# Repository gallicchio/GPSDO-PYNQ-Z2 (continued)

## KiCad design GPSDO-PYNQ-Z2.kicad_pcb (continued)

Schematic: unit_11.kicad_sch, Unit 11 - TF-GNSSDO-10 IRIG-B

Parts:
C1101: 10n C0G; C_0805_2012Metric
C1102, C1104, C1106, C1108: 100n; C_0805_2012Metric
C1103, C1105, C1107, C1109: 10n; C_0805_2012Metric
D1101: BAV99; SOT-23; LCSC C916421; not fitted
J1101: 10MHz IN; SMA_Vertical_THT_Universal; LCSC C496549
J1102: 1pps IN; SMA_Vertical_THT_Universal; LCSC C496549
J1103: TAP IN; U.FL_Hirose_U.FL-R-SMT-1_Vertical; LCSC C88374
J1104: TAP SQ; U.FL_Hirose_U.FL-R-SMT-1_Vertical; LCSC C88374
JP1101: 50R/PARK; PinHeader_1x03_P2.54mm_Vertical
R1101: 51R 1%; R_0805_2012Metric
R1102: 0R; R_0805_2012Metric
R1103: 2k2; R_0805_2012Metric
R1104: 330R; R_0805_2012Metric
R1105: 1M 1%; R_0805_2012Metric
R1106: 51R; R_0805_2012Metric; not fitted
R1107, R1121, R1123: 1k; R_0805_2012Metric
R1108: 10k; R_0805_2012Metric
R1122: 100k; R_0805_2012Metric
R1151, R1152, R1153, R1154: 4R7; R_0805_2012Metric
TP1101: TP_IN; TestPoint_Pad_D1.5mm
TP1102: TP_SQ; TestPoint_Pad_D1.5mm
TP1103: TP_BEAT; TestPoint_Pad_D1.5mm
TP1104: TP_PPS; TestPoint_Pad_D1.5mm
U1101: 74LVC2GU04; SOT-363_SC-70-6; LCSC C116660
U1102, U1103: 74LVC1G80; SOT-23-5; LCSC C42879
U1104: 74LVC1G17; SOT-23-5; LCSC C7836

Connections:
+3V3_A: D1101.1 (K), R1151.1, R1152.1, R1153.1, R1154.1; also elsewhere on the board
/Unit 11/PARK: JP1101.3, R1122.2
/Unit 11/REPLICA: R1105.2, U1101.3 (2A), U1101.4 (2Y)
BEAT_10: TP1103.1, U1103.4 (~Q); also elsewhere on the board
GND: C1102.2, C1103.2, C1104.2, C1105.2, C1106.2, C1107.2, C1108.2, C1109.2, D1101.2 (A), J1101.2 (Ext), J1102.2 (Ext), J1103.2 (Ext), J1104.2 (Ext), JP1101.2, R1103.2, R1106.2, R1108.2, U1101.2 (GND), U1102.3 (GND), U1103.3 (GND), U1104.3 (GND); also elsewhere on the board
HCLK_10: U1102.2 (C), U1103.2 (C); also elsewhere on the board
unnamed: C1101.1, R1102.2, R1103.1, R1121.2
unnamed: C1101.2, D1101.3 (K), R1104.1
unnamed: J1101.1 (In), R1101.1, R1102.1, TP1101.1
unnamed: J1102.1 (In), R1106.1, R1107.1
unnamed: J1103.1 (In), R1121.1
unnamed: J1104.1 (In), R1123.1
unnamed: JP1101.1, R1101.2
unnamed: R1107.2, R1108.1, U1104.2
unnamed: R1104.2, R1105.1, R1122.1, TP1102.1, U1101.1 (1A)
unnamed: R1123.2, U1101.6 (1Y), U1102.1 (D)
unnamed: C1102.1, C1103.1, R1151.2, U1101.5 (VCC)
unnamed: C1104.1, C1105.1, R1152.2, U1102.5 (VCC)
unnamed: U1102.4 (~Q), U1103.1 (D)
unnamed: C1106.1, C1107.1, R1153.2, U1103.5 (VCC)
unnamed: C1108.1, C1109.1, R1154.2, U1104.5 (VCC)
PPS_10: TP1104.1, U1104.4; also elsewhere on the board

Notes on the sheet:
2-3 = PARK: source off or unplugged (not 50R)
into FF1.D: 0/3.3 V CMOS at 10 MHz, edges ~1-2 ns
is plugged in
AC couple
DNP: nothing here drives 50 ohm
REPLICA BIAS. Half 2, its input tied to its output, sits at
10 MHz DDMTD front end + 1 pps front end. Every unit sheet has this same layout; only the names, the per-channel population and the expected levels differ.
DNP clamp: fit only for an unterminated hot source
OUT BEAT_10 -> sheet 'RPi header' OUT PPS_10 -> sheet 'RPi header' IN HELPER_FANOUT <- sheet 'Helper'
its own threshold; the 1M carries that to half 1. One die, one
UNIT 11 - TF-GNSSDO-10 IRIG-B
out: PPS_10, one rising edge per second, 0/3.3 V, straight to the RPi header
supply pin: it decides at its threshold, not 70 mV off (item 18).
1k/10k suits a 3.3 V and a 5 V
1 pps CHANNEL divide -> Schmitt -> straight to the FPGA
jumper is off, and sets the
DC level when nothing
out of FF2: BEAT_10, ~1234 Hz square, 0/3.3 V - its EDGE TIME is the measurement
10 MHz DDMTD CHANNEL terminate -> AC couple -> square -> sample -> retime
bounds the current from a
high-Z source when the
HCLK_10: 10.0012 MHz, 0/3.3 V, this channel's own length-matched branch off the fan-out
pps alike, so no channel differs
1-2 = 50 ohm terminate (ON except ZED-F9T)
neither = a driven, unterminated input
WHY THE 74LVC1G80 The simplest D flip-flop there is: D, CLK, one output and the two rails, and nothing else. No preset and no clear, so there is no asynchronous input that could reset a sampler which must never be reset, and nothing to tie off. Same 74LVC family and the same SOT-23-5 footprint as t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
THE 50R TERM, THE JUMPER SHIPS REMOVED. Fit only if the source drives 50 ohm. A ZED-F9T is DESTROYED by fitting it: its TIMEPULSE pin is 5 mA absolute maximum and 3.3 V into 50R asks for 66 mA. Conversely, leaving it out on an 8 Vpp open-circuit source floats the gate input to about +7.4 V, over th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
AT THE INPUT NODE, before the coupling cap 2.20 Vpp, center 0 V TERMINATED load 51R || 2k2 = 49.8 ohm
THE BAV99 CLAMP IS DNP. Fit only on a channel you will run UNTERMINATED with a source above about 6 Vpp open circuit. It is not fitted by default because its reverse leakage flows in the 1M self-bias resistor: 10 nA is 10 mV of bias shift, leakage roughly doubles every 10 degC, and at 69 mV/ns that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
AT THE GATE, at TP_SQ 2.20 Vpp, center 1.65 V 0.55 to 2.75 V slew 69 mV/ns
DC-COUPLED, DELIBERATELY. The pps widths in this inventory span 1 us (FE-5680A) to 100 ms (ZED-F9T, LBE-1421), and no single AC-coupling RC covers five decades: a 10n/100k network passes the 1 us pulse and droops away to nothing 1% into the 100 ms one. The 1k/10k divider is fitted on EVERY pps chan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
WHY THE 74LVC2GU04 (rev B) TWO unbuffered inverters on one die: half 1 squares, half 2 is its replica bias (item 18). U = UNBUFFERED, one gain stage: three cascaded stages inside a feedback loop oscillate, one cannot. LVC = 5.5 V tolerant inputs on a 3.3 V rail, so a 5 V source survives contact, an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
SCHMITT BUFFER, NOT AN INVERTER. Hysteresis is wrong for the 10 MHz path - it moves the trigger off the zero crossing and turns amplitude into phase - but it is right here: a pps is a rare, fast, possibly noisy edge on a long cable, which is the chatter case hysteresis exists for. No self-bias: a S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
THE SAMPLING FLIP-FLOP (FF1) IS DELIBERATELY ALLOWED TO GO METASTABLE - that is measurement. Never put a synchronizer in front of it. THE RETIMER (FF2) re-clocks on the next helper edge, so what leaves the board is always a clean transition aligned to a helper edge. It costs exactly one helper cycl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
AT THE INPUT 3.3 V or 5 V pps DC coupled, no droop
AFTER THE 1k / 10k 3.00 V or 4.55 V at the Schmitt input

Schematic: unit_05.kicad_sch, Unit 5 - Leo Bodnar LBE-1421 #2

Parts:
C501: 10n C0G; C_0805_2012Metric
C502, C504, C506, C508: 100n; C_0805_2012Metric
C503, C505, C507, C509: 10n; C_0805_2012Metric
D501: BAV99; SOT-23; LCSC C916421; not fitted
J501: 10MHz IN; SMA_Vertical_THT_Universal; LCSC C496549
J502: 1pps IN; SMA_Vertical_THT_Universal; LCSC C496549
J503: TAP IN; U.FL_Hirose_U.FL-R-SMT-1_Vertical; LCSC C88374
J504: TAP SQ; U.FL_Hirose_U.FL-R-SMT-1_Vertical; LCSC C88374
JP501: 50R/PARK; PinHeader_1x03_P2.54mm_Vertical
R501: 51R 1%; R_0805_2012Metric
R502: 0R; R_0805_2012Metric
R503: 2k2; R_0805_2012Metric
R504: 330R; R_0805_2012Metric
R505: 1M 1%; R_0805_2012Metric
R506: 51R; R_0805_2012Metric; not fitted
R507, R521, R523: 1k; R_0805_2012Metric
R508: 10k; R_0805_2012Metric
R522: 100k; R_0805_2012Metric
R551, R552, R553, R554: 4R7; R_0805_2012Metric
TP501: TP_IN; TestPoint_Pad_D1.5mm
TP502: TP_SQ; TestPoint_Pad_D1.5mm
TP503: TP_BEAT; TestPoint_Pad_D1.5mm
TP504: TP_PPS; TestPoint_Pad_D1.5mm
U501: 74LVC2GU04; SOT-363_SC-70-6; LCSC C116660
U502, U503: 74LVC1G80; SOT-23-5; LCSC C42879
U504: 74LVC1G17; SOT-23-5; LCSC C7836

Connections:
+3V3_A: D501.1 (K), R551.1, R552.1, R553.1, R554.1; also elsewhere on the board
/Unit 05/PARK: JP501.3, R522.2
/Unit 05/REPLICA: R505.2, U501.3 (2A), U501.4 (2Y)
BEAT_04: TP503.1, U503.4 (~Q); also elsewhere on the board
GND: C502.2, C503.2, C504.2, C505.2, C506.2, C507.2, C508.2, C509.2, D501.2 (A), J501.2 (Ext), J502.2 (Ext), J503.2 (Ext), J504.2 (Ext), JP501.2, R503.2, R506.2, R508.2, U501.2 (GND), U502.3 (GND), U503.3 (GND), U504.3 (GND); also elsewhere on the board
HCLK_04: U502.2 (C), U503.2 (C); also elsewhere on the board
unnamed: C501.1, R502.2, R503.1, R521.2
unnamed: C501.2, D501.3 (K), R504.1
unnamed: J501.1 (In), R501.1, R502.1, TP501.1
unnamed: J502.1 (In), R506.1, R507.1
unnamed: J503.1 (In), R521.1
unnamed: J504.1 (In), R523.1
unnamed: JP501.1, R501.2
unnamed: R507.2, R508.1, U504.2
unnamed: R504.2, R505.1, R522.1, TP502.1, U501.1 (1A)
unnamed: R523.2, U501.6 (1Y), U502.1 (D)
unnamed: C502.1, C503.1, R551.2, U501.5 (VCC)
unnamed: C504.1, C505.1, R552.2, U502.5 (VCC)
unnamed: U502.4 (~Q), U503.1 (D)
unnamed: C506.1, C507.1, R553.2, U503.5 (VCC)
unnamed: C508.1, C509.1, R554.2, U504.5 (VCC)
PPS_04: TP504.1, U504.4; also elsewhere on the board

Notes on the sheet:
DC level when nothing
UNIT 5 - Leo Bodnar LBE-1421 #2
DNP clamp: fit only for an unterminated hot source
10 MHz DDMTD CHANNEL terminate -> AC couple -> square -> sample -> retime
supply pin: it decides at its threshold, not 70 mV off (item 18).
1 pps CHANNEL divide -> Schmitt -> straight to the FPGA
jumper is off, and sets the
pps alike, so no channel differs
HCLK_04: 10.0012 MHz, 0/3.3 V, this channel's own length-matched branch off the fan-out
out: PPS_04, one rising edge per second, 0/3.3 V, straight to the RPi header
into FF1.D: 0/3.3 V CMOS at 10 MHz, edges ~1-2 ns
AC couple
OUT BEAT_04 -> sheet 'RPi header' OUT PPS_04 -> sheet 'RPi header' IN HELPER_FANOUT <- sheet 'Helper'
bounds the current from a
DNP: nothing here drives 50 ohm
REPLICA BIAS. Half 2, its input tied to its output, sits at
high-Z source when the
1-2 = 50 ohm terminate (ON except ZED-F9T)
its own threshold; the 1M carries that to half 1. One die, one
1k/10k suits a 3.3 V and a 5 V
out of FF2: BEAT_04, ~1234 Hz square, 0/3.3 V - its EDGE TIME is the measurement
2-3 = PARK: source off or unplugged (not 50R)
neither = a driven, unterminated input
is plugged in
10 MHz DDMTD front end + 1 pps front end. Every unit sheet has this same layout; only the names, the per-channel population and the expected levels differ.
DC-COUPLED, DELIBERATELY. The pps widths in this inventory span 1 us (FE-5680A) to 100 ms (ZED-F9T, LBE-1421), and no single AC-coupling RC covers five decades: a 10n/100k network passes the 1 us pulse and droops away to nothing 1% into the 100 ms one. The 1k/10k divider is fitted on EVERY pps chan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
WHY THE 74LVC2GU04 (rev B) TWO unbuffered inverters on one die: half 1 squares, half 2 is its replica bias (item 18). U = UNBUFFERED, one gain stage: three cascaded stages inside a feedback loop oscillate, one cannot. LVC = 5.5 V tolerant inputs on a 3.3 V rail, so a 5 V source survives contact, an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
WHY THE 74LVC1G80 The simplest D flip-flop there is: D, CLK, one output and the two rails, and nothing else. No preset and no clear, so there is no asynchronous input that could reset a sampler which must never be reset, and nothing to tie off. Same 74LVC family and the same SOT-23-5 footprint as t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
AT THE INPUT 3.3 V or 5 V pps DC coupled, no droop
THE BAV99 CLAMP IS DNP. Fit only on a channel you will run UNTERMINATED with a source above about 6 Vpp open circuit. It is not fitted by default because its reverse leakage flows in the 1M self-bias resistor: 10 nA is 10 mV of bias shift, leakage roughly doubles every 10 degC, and at ~820 mV/ns th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
AFTER THE 1k / 10k 3.00 V or 4.55 V at the Schmitt input
THE 50R TERM, THE JUMPER SHIPS REMOVED. Fit only if the source drives 50 ohm. A ZED-F9T is DESTROYED by fitting it: its TIMEPULSE pin is 5 mA absolute maximum and 3.3 V into 50R asks for 66 mA. Conversely, leaving it out on an 8 Vpp open-circuit source floats the gate input to about +7.4 V, over th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
THE SAMPLING FLIP-FLOP (FF1) IS DELIBERATELY ALLOWED TO GO METASTABLE - that is measurement. Never put a synchronizer in front of it. THE RETIMER (FF2) re-clocks on the next helper edge, so what leaves the board is always a clean transition aligned to a helper edge. It costs exactly one helper cycl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
AT THE GATE, at TP_SQ 1.64 Vpp, center 1.65 V 0.83 to 2.47 V slew ~820 mV/ns
SCHMITT BUFFER, NOT AN INVERTER. Hysteresis is wrong for the 10 MHz path - it moves the trigger off the zero crossing and turns amplitude into phase - but it is right here: a pps is a rare, fast, possibly noisy edge on a long cable, which is the chatter case hysteresis exists for. No self-bias: a S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
AT THE INPUT NODE, before the coupling cap 1.64 Vpp, center 0.82 V TERMINATED load 51R || 2k2 = 49.8 ohm

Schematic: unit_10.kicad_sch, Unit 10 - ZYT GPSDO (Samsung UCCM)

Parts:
C1001: 10n C0G; C_0805_2012Metric
C1002, C1004, C1006, C1008: 100n; C_0805_2012Metric
C1003, C1005, C1007, C1009: 10n; C_0805_2012Metric
D1001: BAV99; SOT-23; LCSC C916421; not fitted
J1001: 10MHz IN; SMA_Vertical_THT_Universal; LCSC C496549
J1002: 1pps IN; SMA_Vertical_THT_Universal; LCSC C496549
J1003: TAP IN; U.FL_Hirose_U.FL-R-SMT-1_Vertical; LCSC C88374
J1004: TAP SQ; U.FL_Hirose_U.FL-R-SMT-1_Vertical; LCSC C88374
JP1001: 50R/PARK; PinHeader_1x03_P2.54mm_Vertical
R1001: 51R 1%; R_0805_2012Metric
R1002: 0R; R_0805_2012Metric
R1003: 2k2; R_0805_2012Metric
R1004: 330R; R_0805_2012Metric
R1005: 1M 1%; R_0805_2012Metric
R1006: 51R; R_0805_2012Metric; not fitted
R1007, R1021, R1023: 1k; R_0805_2012Metric
R1008: 10k; R_0805_2012Metric
R1022: 100k; R_0805_2012Metric
R1051, R1052, R1053, R1054: 4R7; R_0805_2012Metric
TP1001: TP_IN; TestPoint_Pad_D1.5mm
TP1002: TP_SQ; TestPoint_Pad_D1.5mm
TP1003: TP_BEAT; TestPoint_Pad_D1.5mm
TP1004: TP_PPS; TestPoint_Pad_D1.5mm
U1001: 74LVC2GU04; SOT-363_SC-70-6; LCSC C116660
U1002, U1003: 74LVC1G80; SOT-23-5; LCSC C42879
U1004: 74LVC1G17; SOT-23-5; LCSC C7836

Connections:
+3V3_A: D1001.1 (K), R1051.1, R1052.1, R1053.1, R1054.1; also elsewhere on the board
/Unit 10/PARK: JP1001.3, R1022.2
/Unit 10/REPLICA: R1005.2, U1001.3 (2A), U1001.4 (2Y)
BEAT_09: TP1003.1, U1003.4 (~Q); also elsewhere on the board
GND: C1002.2, C1003.2, C1004.2, C1005.2, C1006.2, C1007.2, C1008.2, C1009.2, D1001.2 (A), J1001.2 (Ext), J1002.2 (Ext), J1003.2 (Ext), J1004.2 (Ext), JP1001.2, R1003.2, R1006.2, R1008.2, U1001.2 (GND), U1002.3 (GND), U1003.3 (GND), U1004.3 (GND); also elsewhere on the board
HCLK_09: U1002.2 (C), U1003.2 (C); also elsewhere on the board
unnamed: C1001.1, R1002.2, R1003.1, R1021.2
unnamed: C1001.2, D1001.3 (K), R1004.1
unnamed: J1001.1 (In), R1001.1, R1002.1, TP1001.1
unnamed: J1002.1 (In), R1006.1, R1007.1
unnamed: J1003.1 (In), R1021.1
unnamed: J1004.1 (In), R1023.1
unnamed: JP1001.1, R1001.2
unnamed: R1007.2, R1008.1, U1004.2
unnamed: R1004.2, R1005.1, R1022.1, TP1002.1, U1001.1 (1A)
unnamed: R1023.2, U1001.6 (1Y), U1002.1 (D)
unnamed: C1002.1, C1003.1, R1051.2, U1001.5 (VCC)
unnamed: C1004.1, C1005.1, R1052.2, U1002.5 (VCC)
unnamed: U1002.4 (~Q), U1003.1 (D)
unnamed: C1006.1, C1007.1, R1053.2, U1003.5 (VCC)
unnamed: C1008.1, C1009.1, R1054.2, U1004.5 (VCC)
PPS_09: TP1004.1, U1004.4; also elsewhere on the board

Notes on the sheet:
into FF1.D: 0/3.3 V CMOS at 10 MHz, edges ~1-2 ns
its own threshold; the 1M carries that to half 1. One die, one
1 pps CHANNEL divide -> Schmitt -> straight to the FPGA
pps alike, so no channel differs
neither = a driven, unterminated input
out of FF2: BEAT_09, ~1234 Hz square, 0/3.3 V - its EDGE TIME is the measurement
jumper is off, and sets the
DNP: nothing here drives 50 ohm
10 MHz DDMTD front end + 1 pps front end. Every unit sheet has this same layout; only the names, the per-channel population and the expected levels differ.
1-2 = 50 ohm terminate (ON except ZED-F9T)
supply pin: it decides at its threshold, not 70 mV off (item 18).
is plugged in
DC level when nothing
OUT BEAT_09 -> sheet 'RPi header' OUT PPS_09 -> sheet 'RPi header' IN HELPER_FANOUT <- sheet 'Helper'
HCLK_09: 10.0012 MHz, 0/3.3 V, this channel's own length-matched branch off the fan-out
REPLICA BIAS. Half 2, its input tied to its output, sits at
high-Z source when the
1k/10k suits a 3.3 V and a 5 V
bounds the current from a
UNIT 10 - ZYT GPSDO (Samsung UCCM)
out: PPS_09, one rising edge per second, 0/3.3 V, straight to the RPi header
DNP clamp: fit only for an unterminated hot source
AC couple
10 MHz DDMTD CHANNEL terminate -> AC couple -> square -> sample -> retime
2-3 = PARK: source off or unplugged (not 50R)
AFTER THE 1k / 10k 3.00 V or 4.55 V at the Schmitt input
AT THE GATE, at TP_SQ 1.50 Vpp, center 1.65 V 0.90 to 2.40 V slew 47 mV/ns
AT THE INPUT NODE, before the coupling cap 1.50 Vpp, center 0 V TERMINATED load 51R || 2k2 = 49.8 ohm
AT THE INPUT 3.3 V or 5 V pps DC coupled, no droop
WHY THE 74LVC1G80 The simplest D flip-flop there is: D, CLK, one output and the two rails, and nothing else. No preset and no clear, so there is no asynchronous input that could reset a sampler which must never be reset, and nothing to tie off. Same 74LVC family and the same SOT-23-5 footprint as t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
THE SAMPLING FLIP-FLOP (FF1) IS DELIBERATELY ALLOWED TO GO METASTABLE - that is measurement. Never put a synchronizer in front of it. THE RETIMER (FF2) re-clocks on the next helper edge, so what leaves the board is always a clean transition aligned to a helper edge. It costs exactly one helper cycl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
SCHMITT BUFFER, NOT AN INVERTER. Hysteresis is wrong for the 10 MHz path - it moves the trigger off the zero crossing and turns amplitude into phase - but it is right here: a pps is a rare, fast, possibly noisy edge on a long cable, which is the chatter case hysteresis exists for. No self-bias: a S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
DC-COUPLED, DELIBERATELY. The pps widths in this inventory span 1 us (FE-5680A) to 100 ms (ZED-F9T, LBE-1421), and no single AC-coupling RC covers five decades: a 10n/100k network passes the 1 us pulse and droops away to nothing 1% into the 100 ms one. The 1k/10k divider is fitted on EVERY pps chan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
THE 50R TERM, THE JUMPER SHIPS REMOVED. Fit only if the source drives 50 ohm. A ZED-F9T is DESTROYED by fitting it: its TIMEPULSE pin is 5 mA absolute maximum and 3.3 V into 50R asks for 66 mA. Conversely, leaving it out on an 8 Vpp open-circuit source floats the gate input to about +7.4 V, over th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
WHY THE 74LVC2GU04 (rev B) TWO unbuffered inverters on one die: half 1 squares, half 2 is its replica bias (item 18). U = UNBUFFERED, one gain stage: three cascaded stages inside a feedback loop oscillate, one cannot. LVC = 5.5 V tolerant inputs on a 3.3 V rail, so a 5 V source survives contact, an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
THE BAV99 CLAMP IS DNP. Fit only on a channel you will run UNTERMINATED with a source above about 6 Vpp open circuit. It is not fitted by default because its reverse leakage flows in the 1M self-bias resistor: 10 nA is 10 mV of bias shift, leakage roughly doubles every 10 degC, and at 47 mV/ns that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

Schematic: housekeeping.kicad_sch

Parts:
C5001, C5003, C5005, C5007, C5009, C5011, C5013, C5015, C5017: 100n; C_0805_2012Metric
C5002, C5004, C5006, C5008, C5010, C5012, C5014, C5016, C5018: 10n; C_0805_2012Metric
J5001: debug 2x10; PinHeader_2x10_P2.54mm_Vertical
R5001: 100R; R_0805_2012Metric
R5002: 100k; R_0805_2012Metric
R5051, R5052, R5053, R5054, R5055, R5056, R5057, R5058, R5059: 4R7; R_0805_2012Metric
U5001, U5002, U5003, U5004, U5005, U5006, U5007, U5008: TMP1075D; SOIC-8_3.9x4.9mm_P1.27mm; LCSC C2878381
U5009: MCP4725A0T-E/CH; SOT-23-6; LCSC C144198

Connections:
+3V3_A: J5001.5; also elsewhere on the board
+3V3_D: J5001.7, R5051.1, R5052.1, R5053.1, R5054.1, R5055.1, R5056.1, R5057.1, R5058.1, R5059.1, U5002.7 (A0), U5003.6 (A1), U5004.6 (A1), U5004.7 (A0), U5005.5 (A2), U5006.5 (A2), U5006.7 (A0), U5007.5 (A2), U5007.6 (A1), U5008.5 (A2), U5008.6 (A1), U5008.7 (A0), U5009.6 (A0); also elsewhere on the board
+5V_HDR: J5001.1; also elsewhere on the board
GND: C5001.2, C5002.2, C5003.2, C5004.2, C5005.2, C5006.2, C5007.2, C5008.2, C5009.2, C5010.2, C5011.2, C5012.2, C5013.2, C5014.2, C5015.2, C5016.2, C5017.2, C5018.2, J5001.2, J5001.4, J5001.6, J5001.8, J5001.10, J5001.12, J5001.14, J5001.16, J5001.18, J5001.20, R5002.2, U5001.4 (GND), U5001.5 (A2), U5001.6 (A1), U5001.7 (A0), U5002.4 (GND), U5002.5 (A2), U5002.6 (A1), U5003.4 (GND), U5003.5 (A2), U5003.7 (A0), U5004.4 (GND), U5004.5 (A2), U5005.4 (GND), U5005.6 (A1), U5005.7 (A0), U5006.4 (GND), U5006.6 (A1), U5007.4 (GND), U5007.7 (A0), U5008.4 (GND), U5009.2 (VSS); also elsewhere on the board
HTR_DRIVE: J5001.9, R5001.2, R5002.1; also elsewhere on the board
I2C_SCL: J5001.13, U5001.2 (SCL), U5002.2 (SCL), U5003.2 (SCL), U5004.2 (SCL), U5005.2 (SCL), U5006.2 (SCL), U5007.2 (SCL), U5008.2 (SCL), U5009.5 (SCL); also elsewhere on the board
I2C_SDA: J5001.11, U5001.1 (SDA), U5002.1 (SDA), U5003.1 (SDA), U5004.1 (SDA), U5005.1 (SDA), U5006.1 (SDA), U5007.1 (SDA), U5008.1 (SDA), U5009.4 (SDA); also elsewhere on the board
unnamed: C5001.1, C5002.1, R5051.2, U5001.8 (V+)
unnamed: C5003.1, C5004.1, R5052.2, U5002.8 (V+)
unnamed: C5005.1, C5006.1, R5053.2, U5003.8 (V+)
unnamed: C5007.1, C5008.1, R5054.2, U5004.8 (V+)
unnamed: C5009.1, C5010.1, R5055.2, U5005.8 (V+)
unnamed: C5011.1, C5012.1, R5056.2, U5006.8 (V+)
unnamed: C5013.1, C5014.1, R5057.2, U5007.8 (V+)
unnamed: C5015.1, C5016.1, R5058.2, U5008.8 (V+)
unnamed: C5017.1, C5018.1, R5059.2, U5009.3 (VDD)
unnamed: R5001.1, U5009.1 (VOUT)
ONEWIRE: J5001.3; also elsewhere on the board

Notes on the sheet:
HOUSEKEEPING
0x4D
0x4C
0x4E
left edge, between units 5 and 7
bottom-left corner, below unit 13
HEATER DAC
left edge, by unit 1
Eight board thermometers, the heater DAC and the debug header - all on the two I2C pins we already spend, so none of this costs a header pin.
0x48
right edge, by unit 2
I2C bus, 100 kHz. Pull-ups are on the PYNQ-Z2 (2k2 on header pins 3 and 5), so none here.
right edge, by unit 6
EIGHT BOARD THERMOMETERS TMP1075D, SOIC-8, 8 addresses from A2:A0
DEBUG HEADER 2x10, 0.1in, signal/ground alternating
left edge, by unit 11
right edge, between units 10 and 12
0x4F
0x49
centre line, beside the helper fan-out
0x4A
0x4B
WHAT THE GATE DOES BEFORE SOFTWARE WRITES THE DAC. The 100k holds all three gates down whenever the DAC is not driving them, which covers an unpopulated or unpowered DAC and the moment before the first I2C write. It does NOT cover the DAC powering up from its own EEPROM into something other than ze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
WHY EIGHT, AND WHY ON THE BOARD. Every threshold on this board moves with temperature, and the movement is meant to be common mode because all thirteen channels share one rail and one die family. Common mode is a claim, not a fact, and these eight sensors are how it gets tested: four corners give t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
THE ADDRESS MAP IS THE POSITION MAP. A2:A0 are strapped to the binary index, so the part at 0x48 is the leftmost here and the leftmost on the board, and the software never needs a lookup table telling it which sensor is where. The eight span 0x48-0x4F, which is the whole TMP1075 address space: ther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
A ground on every even pin, so a scope probe's spring ground reaches the signal beside it without a clip lead - which would otherwise show you its own loop rather than the signal. WHAT IS DELIBERATELY NOT HERE: any beat, pps or clock. This header sits at the far edge, so tapping one would hang a 15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
WHY A DAC AND A LINEAR PASS FET, AND NOT PWM. PWM is the cheap way to drive a heater and it is the wrong way here. Switching amperes of heater current a few hundred times a second puts that fundamental and its harmonics into the ground plane and into the supply, and this board's whole job is measur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
12-bit DAC straight onto the pass FET's gate. The temperature loop runs in Python on the PYNQ: read a TMP1075, write the DAC, integrate. Nothing switches, and it costs no header pins because it shares the I2C bus with the thermometers.

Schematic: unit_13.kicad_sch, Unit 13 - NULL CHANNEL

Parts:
C1301: 10n C0G; C_0805_2012Metric
C1302, C1304, C1306: 100n; C_0805_2012Metric
C1303, C1305, C1307: 10n; C_0805_2012Metric
D1301: BAV99; SOT-23; LCSC C916421; not fitted
J1301: 10MHz IN; SMA_Vertical_THT_Universal; LCSC C496549
J1303: TAP IN; U.FL_Hirose_U.FL-R-SMT-1_Vertical; LCSC C88374
J1304: TAP SQ; U.FL_Hirose_U.FL-R-SMT-1_Vertical; LCSC C88374
JP1301: 50R/PARK; PinHeader_1x03_P2.54mm_Vertical
R1301: 51R 1%; R_0805_2012Metric
R1302: 0R; R_0805_2012Metric
R1303: 2k2; R_0805_2012Metric
R1304: 330R; R_0805_2012Metric
R1305: 1M 1%; R_0805_2012Metric
R1321, R1323: 1k; R_0805_2012Metric
R1322: 100k; R_0805_2012Metric
R1351, R1352, R1353: 4R7; R_0805_2012Metric
TP1301: TP_IN; TestPoint_Pad_D1.5mm
TP1302: TP_SQ; TestPoint_Pad_D1.5mm
TP1303: TP_BEAT; TestPoint_Pad_D1.5mm
U1301: 74LVC2GU04; SOT-363_SC-70-6; LCSC C116660
U1302, U1303: 74LVC1G80; SOT-23-5; LCSC C42879

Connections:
+3V3_A: D1301.1 (K), R1351.1, R1352.1, R1353.1; also elsewhere on the board
/Unit 13/PARK: JP1301.3, R1322.2
/Unit 13/REPLICA: R1305.2, U1301.3 (2A), U1301.4 (2Y)
BEAT_12: TP1303.1, U1303.4 (~Q); also elsewhere on the board
GND: C1302.2, C1303.2, C1304.2, C1305.2, C1306.2, C1307.2, D1301.2 (A), J1301.2 (Ext), J1303.2 (Ext), J1304.2 (Ext), JP1301.2, R1303.2, U1301.2 (GND), U1302.3 (GND), U1303.3 (GND); also elsewhere on the board
HCLK_12: U1302.2 (C), U1303.2 (C); also elsewhere on the board
unnamed: C1301.1, R1302.2, R1303.1, R1321.2
unnamed: C1301.2, D1301.3 (K), R1304.1
unnamed: J1301.1 (In), R1301.1, R1302.1, TP1301.1
unnamed: J1303.1 (In), R1321.1
unnamed: J1304.1 (In), R1323.1
unnamed: JP1301.1, R1301.2
unnamed: R1304.2, R1305.1, R1322.1, TP1302.1, U1301.1 (1A)
unnamed: R1323.2, U1301.6 (1Y), U1302.1 (D)
unnamed: C1302.1, C1303.1, R1351.2, U1301.5 (VCC)
unnamed: C1304.1, C1305.1, R1352.2, U1302.5 (VCC)
unnamed: U1302.4 (~Q), U1303.1 (D)
unnamed: C1306.1, C1307.1, R1353.2, U1303.5 (VCC)

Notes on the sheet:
is plugged in
10 MHz DDMTD front end + 1 pps front end. Every unit sheet has this same layout; only the names, the per-channel population and the expected levels differ.
1-2 = 50 ohm terminate (ON except ZED-F9T)
into FF1.D: 0/3.3 V CMOS at 10 MHz, edges ~1-2 ns
AC couple
supply pin: it decides at its threshold, not 70 mV off (item 18).
2-3 = PARK: source off or unplugged (not 50R)
neither = a driven, unterminated input
jumper is off, and sets the
UNIT 13 - NULL CHANNEL
DC level when nothing
out of FF2: BEAT_12, ~1234 Hz square, 0/3.3 V - its EDGE TIME is the measurement
REPLICA BIAS. Half 2, its input tied to its output, sits at
DNP clamp: fit only for an unterminated hot source
its own threshold; the 1M carries that to half 1. One die, one
high-Z source when the
10 MHz DDMTD CHANNEL terminate -> AC couple -> square -> sample -> retime
OUT BEAT_12 -> sheet 'RPi header' (this unit has no pps) IN HELPER_FANOUT <- sheet 'Helper'
bounds the current from a
HCLK_12: 10.0012 MHz, 0/3.3 V, this channel's own length-matched branch off the fan-out
WHY THE 74LVC1G80 The simplest D flip-flop there is: D, CLK, one output and the two rails, and nothing else. No preset and no clear, so there is no asynchronous input that could reset a sampler which must never be reset, and nothing to tie off. Same 74LVC family and the same SOT-23-5 footprint as t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
PER-CHANNEL NOTE Instrument-only null. No pps. Round 25: this used to say the source was 'selected by JP_NULL - see the helper sheet'. There is no JP_NULL, on the helper sheet or anywhere else -- unit 13 is an ordinary channel with its own SMA (J1301). You make it a null by CABLING J3001, the CLK1 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
THE 50R TERM, THE JUMPER SHIPS REMOVED. Fit only if the source drives 50 ohm. A ZED-F9T is DESTROYED by fitting it: its TIMEPULSE pin is 5 mA absolute maximum and 3.3 V into 50R asks for 66 mA. Conversely, leaving it out on an 8 Vpp open-circuit source floats the gate input to about +7.4 V, over th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
AT THE INPUT NODE, before the coupling cap 1.65 Vpp, center 0.82 V TERMINATED load 51R || 2k2 = 49.8 ohm
1 pps front end deliberately omitted on unit 13. This is the NULL channel. It exists to measure the instrument rather than a GPSDO, so there is no pps to time. The circuit that would sit here on units 1 to 12 is drawn in exactly the same place on every other unit sheet, so that paging through this 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
WHY THE 74LVC2GU04 (rev B) TWO unbuffered inverters on one die: half 1 squares, half 2 is its replica bias (item 18). U = UNBUFFERED, one gain stage: three cascaded stages inside a feedback loop oscillate, one cannot. LVC = 5.5 V tolerant inputs on a 3.3 V rail, so a 5 V source survives contact, an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
AT THE GATE, at TP_SQ 1.65 Vpp, center 1.65 V 0.82 to 2.47 V slew ~825 mV/ns
THE BAV99 CLAMP IS DNP. Fit only on a channel you will run UNTERMINATED with a source above about 6 Vpp open circuit. It is not fitted by default because its reverse leakage flows in the 1M self-bias resistor: 10 nA is 10 mV of bias shift, leakage roughly doubles every 10 degC, and at ~825 mV/ns th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
THE SAMPLING FLIP-FLOP (FF1) IS DELIBERATELY ALLOWED TO GO METASTABLE - that is measurement. Never put a synchronizer in front of it. THE RETIMER (FF2) re-clocks on the next helper edge, so what leaves the board is always a clean transition aligned to a helper edge. It costs exactly one helper cycl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

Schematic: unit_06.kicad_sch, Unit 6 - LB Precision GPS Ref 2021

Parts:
C601: 10n C0G; C_0805_2012Metric
C602, C604, C606, C608: 100n; C_0805_2012Metric
C603, C605, C607, C609: 10n; C_0805_2012Metric
D601: BAV99; SOT-23; LCSC C916421; not fitted
J601: 10MHz IN; SMA_Vertical_THT_Universal; LCSC C496549
J602: 1pps IN; SMA_Vertical_THT_Universal; LCSC C496549
J603: TAP IN; U.FL_Hirose_U.FL-R-SMT-1_Vertical; LCSC C88374
J604: TAP SQ; U.FL_Hirose_U.FL-R-SMT-1_Vertical; LCSC C88374
JP601: 50R/PARK; PinHeader_1x03_P2.54mm_Vertical
R601: 51R 1%; R_0805_2012Metric
R602: 0R; R_0805_2012Metric
R603: 2k2; R_0805_2012Metric
R604: 330R; R_0805_2012Metric
R605: 1M 1%; R_0805_2012Metric
R606: 51R; R_0805_2012Metric; not fitted
R607, R621, R623: 1k; R_0805_2012Metric
R608: 10k; R_0805_2012Metric
R622: 100k; R_0805_2012Metric
R651, R652, R653, R654: 4R7; R_0805_2012Metric
TP601: TP_IN; TestPoint_Pad_D1.5mm
TP602: TP_SQ; TestPoint_Pad_D1.5mm
TP603: TP_BEAT; TestPoint_Pad_D1.5mm
TP604: TP_PPS; TestPoint_Pad_D1.5mm
U601: 74LVC2GU04; SOT-363_SC-70-6; LCSC C116660
U602, U603: 74LVC1G80; SOT-23-5; LCSC C42879
U604: 74LVC1G17; SOT-23-5; LCSC C7836

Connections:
+3V3_A: D601.1 (K), R651.1, R652.1, R653.1, R654.1; also elsewhere on the board
/Unit 06/PARK: JP601.3, R622.2
/Unit 06/REPLICA: R605.2, U601.3 (2A), U601.4 (2Y)
BEAT_05: TP603.1, U603.4 (~Q); also elsewhere on the board
GND: C602.2, C603.2, C604.2, C605.2, C606.2, C607.2, C608.2, C609.2, D601.2 (A), J601.2 (Ext), J602.2 (Ext), J603.2 (Ext), J604.2 (Ext), JP601.2, R603.2, R606.2, R608.2, U601.2 (GND), U602.3 (GND), U603.3 (GND), U604.3 (GND); also elsewhere on the board
HCLK_05: U602.2 (C), U603.2 (C); also elsewhere on the board
unnamed: C601.1, R602.2, R603.1, R621.2
unnamed: C601.2, D601.3 (K), R604.1
unnamed: J601.1 (In), R601.1, R602.1, TP601.1
unnamed: J602.1 (In), R606.1, R607.1
unnamed: J603.1 (In), R621.1
unnamed: J604.1 (In), R623.1
unnamed: JP601.1, R601.2
unnamed: R607.2, R608.1, U604.2
unnamed: R604.2, R605.1, R622.1, TP602.1, U601.1 (1A)
unnamed: R623.2, U601.6 (1Y), U602.1 (D)
unnamed: C602.1, C603.1, R651.2, U601.5 (VCC)
unnamed: C604.1, C605.1, R652.2, U602.5 (VCC)
unnamed: U602.4 (~Q), U603.1 (D)
unnamed: C606.1, C607.1, R653.2, U603.5 (VCC)
unnamed: C608.1, C609.1, R654.2, U604.5 (VCC)
PPS_05: TP604.1, U604.4; also elsewhere on the board

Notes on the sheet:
neither = a driven, unterminated input
out of FF2: BEAT_05, ~1234 Hz square, 0/3.3 V - its EDGE TIME is the measurement
is plugged in
DNP: nothing here drives 50 ohm
into FF1.D: 0/3.3 V CMOS at 10 MHz, edges ~1-2 ns
bounds the current from a
1-2 = 50 ohm terminate (ON except ZED-F9T)
pps alike, so no channel differs
10 MHz DDMTD front end + 1 pps front end. Every unit sheet has this same layout; only the names, the per-channel population and the expected levels differ.
2-3 = PARK: source off or unplugged (not 50R)
high-Z source when the
its own threshold; the 1M carries that to half 1. One die, one
DC level when nothing
REPLICA BIAS. Half 2, its input tied to its output, sits at
AC couple
OUT BEAT_05 -> sheet 'RPi header' OUT PPS_05 -> sheet 'RPi header' IN HELPER_FANOUT <- sheet 'Helper'
supply pin: it decides at its threshold, not 70 mV off (item 18).
out: PPS_05, one rising edge per second, 0/3.3 V, straight to the RPi header
HCLK_05: 10.0012 MHz, 0/3.3 V, this channel's own length-matched branch off the fan-out
1 pps CHANNEL divide -> Schmitt -> straight to the FPGA
DNP clamp: fit only for an unterminated hot source
1k/10k suits a 3.3 V and a 5 V
jumper is off, and sets the
10 MHz DDMTD CHANNEL terminate -> AC couple -> square -> sample -> retime
UNIT 6 - LB Precision GPS Ref 2021
AFTER THE 1k / 10k 3.00 V or 4.55 V at the Schmitt input
WHY THE 74LVC1G80 The simplest D flip-flop there is: D, CLK, one output and the two rails, and nothing else. No preset and no clear, so there is no asynchronous input that could reset a sampler which must never be reset, and nothing to tie off. Same 74LVC family and the same SOT-23-5 footprint as t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
WHY THE 74LVC2GU04 (rev B) TWO unbuffered inverters on one die: half 1 squares, half 2 is its replica bias (item 18). U = UNBUFFERED, one gain stage: three cascaded stages inside a feedback loop oscillate, one cannot. LVC = 5.5 V tolerant inputs on a 3.3 V rail, so a 5 V source survives contact, an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
SCHMITT BUFFER, NOT AN INVERTER. Hysteresis is wrong for the 10 MHz path - it moves the trigger off the zero crossing and turns amplitude into phase - but it is right here: a pps is a rare, fast, possibly noisy edge on a long cable, which is the chatter case hysteresis exists for. No self-bias: a S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
THE SAMPLING FLIP-FLOP (FF1) IS DELIBERATELY ALLOWED TO GO METASTABLE - that is measurement. Never put a synchronizer in front of it. THE RETIMER (FF2) re-clocks on the next helper edge, so what leaves the board is always a clean transition aligned to a helper edge. It costs exactly one helper cycl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
DC-COUPLED, DELIBERATELY. The pps widths in this inventory span 1 us (FE-5680A) to 100 ms (ZED-F9T, LBE-1421), and no single AC-coupling RC covers five decades: a 10n/100k network passes the 1 us pulse and droops away to nothing 1% into the 100 ms one. The 1k/10k divider is fitted on EVERY pps chan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
THE 50R TERM, THE JUMPER SHIPS REMOVED. Fit only if the source drives 50 ohm. A ZED-F9T is DESTROYED by fitting it: its TIMEPULSE pin is 5 mA absolute maximum and 3.3 V into 50R asks for 66 mA. Conversely, leaving it out on an 8 Vpp open-circuit source floats the gate input to about +7.4 V, over th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
AT THE GATE, at TP_SQ 2.30 Vpp, center 1.65 V 0.50 to 2.80 V slew ~1150 mV/ns
AT THE INPUT 3.3 V or 5 V pps DC coupled, no droop
AT THE INPUT NODE, before the coupling cap 2.30 Vpp, center 1.15 V TERMINATED load 51R || 2k2 = 49.8 ohm
THE BAV99 CLAMP IS DNP. Fit only on a channel you will run UNTERMINATED with a source above about 6 Vpp open circuit. It is not fitted by default because its reverse leakage flows in the 1M self-bias resistor: 10 nA is 10 mV of bias shift, leakage roughly doubles every 10 degC, and at ~1150 mV/ns t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

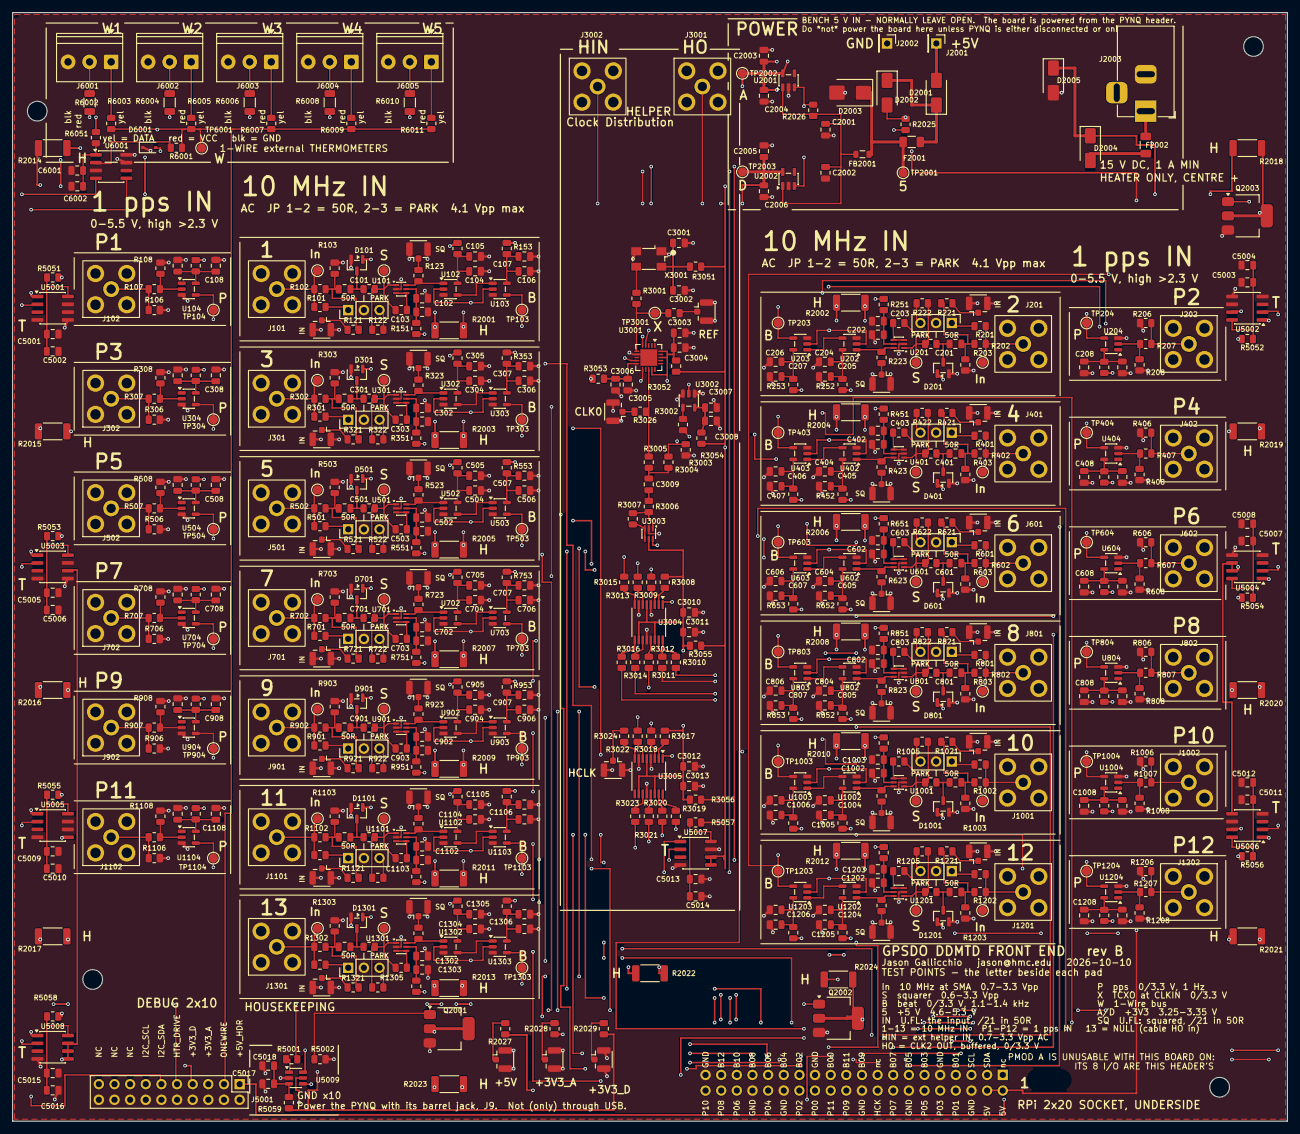
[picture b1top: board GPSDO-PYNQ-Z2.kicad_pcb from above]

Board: 4 copper layers, 207.0 x 180.0 mm, 666 parts (1 on the bottom side), 338 nets.

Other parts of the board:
MH1, MH2, MH3, MH4: MountingHole_M3_NPTH
MH5: MountingSlot_M3_NPTH

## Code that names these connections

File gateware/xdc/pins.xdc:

# Pin constraints for the GPSDO DDMTD front end on a PYNQ-Z2.
#
# GENERATED by gateware/gen_xdc.py from gen/design.py -- do not edit.
# 2026-09-14
#
# Every ball here was cross-checked in round 22 against the TUL
# schematic R12 sheet 4 and the PYNQ-Z2 Reference Manual v1.0.  Note
# that eight of these balls are SHARED WITH PMOD A, so Pmod A cannot be
# used while this board is fitted.

# ---- the helper clock -------------------------------------------
#
# Header pin 18, the only clock-capable pin on the Raspberry Pi header
# on BOTH the PYNQ-Z2 and the Icepi Zero.  gen/design.py asserts that
# nothing may reassign it.
#
# The PYNQ puts a 200 ohm series resistor in every header GPIO, which
# with the FPGA's input capacitance gives this clock a ~4.4 ns edge at
# the die.  That is slow for a clock input; if bring-up shows double
# clocking, that resistor is the reason.
set_property -dict {PACKAGE_PIN Y7 IOSTANDARD LVCMOS33} [get_ports {helper_clk}]  ;# header pin 18
create_clock -period 99.988 -name helper_clk [get_ports {helper_clk}]  ;# 10.0012344 MHz

# ---- the thirteen beats, ~1234 Hz ---------------------------------
set_property -dict {PACKAGE_PIN W10  IOSTANDARD LVCMOS33} [get_ports {beat[0]}]   ;# BEAT_00  header pin 23
set_property -dict {PACKAGE_PIN Y18  IOSTANDARD LVCMOS33} [get_ports {beat[1]}]   ;# BEAT_01  header pin 7
set_property -dict {PACKAGE_PIN Y16  IOSTANDARD LVCMOS33} [get_ports {beat[2]}]   ;# BEAT_02  header pin 27
set_property -dict {PACKAGE_PIN U7   IOSTANDARD LVCMOS33} [get_ports {beat[3]}]   ;# BEAT_03  header pin 11
set_property -dict {PACKAGE_PIN Y19  IOSTANDARD LVCMOS33} [get_ports {beat[4]}]   ;# BEAT_04  header pin 29
set_property -dict {PACKAGE_PIN V7   IOSTANDARD LVCMOS33} [get_ports {beat[5]}]   ;# BEAT_05  header pin 13
set_property -dict {PACKAGE_PIN U18  IOSTANDARD LVCMOS33} [get_ports {beat[6]}]   ;# BEAT_06  header pin 31
set_property -dict {PACKAGE_PIN U8   IOSTANDARD LVCMOS33} [get_ports {beat[7]}]   ;# BEAT_07  header pin 15
set_property -dict {PACKAGE_PIN W8   IOSTANDARD LVCMOS33} [get_ports {beat[8]}]   ;# BEAT_08  header pin 33
set_property -dict {PACKAGE_PIN V8   IOSTANDARD LVCMOS33} [get_ports {beat[9]}]   ;# BEAT_09  header pin 19
set_property -dict {PACKAGE_PIN Y8   IOSTANDARD LVCMOS33} [get_ports {beat[10]}]   ;# BEAT_10  header pin 35
set_property -dict {PACKAGE_PIN V10  IOSTANDARD LVCMOS33} [get_ports {beat[11]}]   ;# BEAT_11  header pin 21
set_property -dict {PACKAGE_PIN W9   IOSTANDARD LVCMOS33} [get_ports {beat[12]}]   ;# BEAT_12  header pin 37

# ---- the twelve pps returns, 1 Hz ---------------------------------
# There is no PPS_12: unit 13 is the null channel and has no pps.
set_property -dict {PACKAGE_PIN U19  IOSTANDARD LVCMOS33} [get_ports {pps[0]}]    ;# PPS_00   header pin 26
set_property -dict {PACKAGE_PIN V6   IOSTANDARD LVCMOS33} [get_ports {pps[1]}]    ;# PPS_01   header pin 8
set_property -dict {PACKAGE_PIN Y17  IOSTANDARD LVCMOS33} [get_ports {pps[2]}]    ;# PPS_02   header pin 28
set_property -dict {PACKAGE_PIN Y6   IOSTANDARD LVCMOS33} [get_ports {pps[3]}]    ;# PPS_03   header pin 10
set_property -dict {PACKAGE_PIN B20  IOSTANDARD LVCMOS33} [get_ports {pps[4]}]    ;# PPS_04   header pin 32
set_property -dict {PACKAGE_PIN C20  IOSTANDARD LVCMOS33} [get_ports {pps[5]}]    ;# PPS_05   header pin 12
set_property -dict {PACKAGE_PIN B19  IOSTANDARD LVCMOS33} [get_ports {pps[6]}]    ;# PPS_06   header pin 36
set_property -dict {PACKAGE_PIN W6   IOSTANDARD LVCMOS33} [get_ports {pps[7]}]    ;# PPS_07   header pin 16
set_property -dict {PACKAGE_PIN A20  IOSTANDARD LVCMOS33} [get_ports {pps[8]}]    ;# PPS_08   header pin 38
set_property -dict {PACKAGE_PIN F20  IOSTANDARD LVCMOS33} [get_ports {pps[9]}]    ;# PPS_09   header pin 22
set_property -dict {PACKAGE_PIN Y9   IOSTANDARD LVCMOS33} [get_ports {pps[10]}]    ;# PPS_10   header pin 40
set_property -dict {PACKAGE_PIN F19  IOSTANDARD LVCMOS33} [get_ports {pps[11]}]    ;# PPS_11   header pin 24

# ---- I2C to the Si5351, the thermometers, the DAC and the bridge --
# 2k2 pull-ups are already fitted on the PYNQ (R305-R308); the front-end
# board deliberately fits none.
set_property -dict {PACKAGE_PIN W18  IOSTANDARD LVCMOS33 PULLUP true} [get_ports {iic_sda_io}]  ;# I2C_SDA  header pin 3
set_property -dict {PACKAGE_PIN W19  IOSTANDARD LVCMOS33 PULLUP true} [get_ports {iic_scl_io}]  ;# I2C_SCL  header pin 5

# ---- timing ------------------------------------------------------
# Beats and pps are asynchronous to the PS clock and are taken into the
# helper domain through two-flop synchronisers, so they are declared
# false paths.  The measurement does NOT depend on their setup/hold
# against the helper: it depends on the counter value latched when the
# synchroniser sees the edge.
set_false_path -from [get_ports {beat[*]}]
set_false_path -from [get_ports {pps[*]}]

# The helper comes from the Si5351 on the front-end board and is not
# phase-related to anything inside the FPGA.  Without this Vivado tries
# to time every timestamp bit crossing out of the helper domain and
# reports thousands of failing endpoints that mean nothing -- the
# crossing is handled by the toggle-synchroniser in dmtd_capture, not by
# timing closure.
#
# The second group is 'every other clock' rather than clk_fpga_0 by
# name, so this is still correct for the bring-up variant, which runs
# the AXI fabric from the board's own 125 MHz oscillator instead.
#
# ONE group, deliberately.  set_clock_groups with a single -group means
# 'this group is asynchronous to every other clock in the design', and
# that is resolved at analysis time rather than when this file is read.
# Naming the other clocks -- or computing them from all_clocks -- makes
# the constraint depend on XDC ordering, and a clock created later (the
# PS7's clk_fpga_0, an MMCM output) then silently falls outside the
# group.  The symptom is thousands of failing CDC endpoints in a timing
# report that points at the design instead of at the constraint.
if {![llength [get_clocks -quiet helper_clk]]} {
    error "pins.xdc: helper_clk is not defined -- the create_clock above\
 did not match a port, so nothing below constrains anything."
}
set_clock_groups -asynchronous \
    -group [get_clocks -include_generated_clocks helper_clk]

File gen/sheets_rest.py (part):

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    s.wire(XEN, y, XEN, 107.95)                       # +5V_HDR down to R2025 pin 1
    s.wire(XEN, 115.57, XEN, YEN)                     # R2025 pin 2 down to the bus
    s.wire(XEN, YEN, 300.0, YEN)                      # the LDO_EN bus
    s.glabel(300.0, YEN, "LDO_EN", shape="passive", justify="left")
    s.junction(XOVR, y)
    s.wire(XOVR, y, XOVR, 107.95)                     # input bus down to R2026 pin 1
    s.wire(XOVR, 115.57, XOVR, YEN)                   # R2026 pin 2 down to the bus
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                  lcsc="C209902", ref_dxy=(7.62, -5.08), val_dxy=(7.62, -2.54))
        s.wire(gx[-1] + 15.24, by, gx[-1] + 15.24, q.pin(2)[1])
        s.wire(gx[-1] + 15.24, q.pin(2)[1], *q.pin(2))
        s.glabel(q.pin(1)[0] - 20.32, q.pin(1)[1], "HTR_DRIVE", shape="input",
                 justify="right")
        s.wire(q.pin(1)[0] - 20.32, q.pin(1)[1], *q.pin(1))
        gnd(s, *q.pin(3), drop=8.89, R=R)
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           "ground at exactly one point", size=1.4, italic=True)

    # The two LDO_EN resistors, created last so they are R2025 and R2026 (see
    # the note beside the LDO_EN bus above).  Pins land at 107.95 and 115.57.
    r_v(s, XEN, 111.76, R("R"), "10k")                     # R2025: +5V_HDR -> LDO_EN
    r_v(s, XOVR, 111.76, R("R"), "0R", dnp=True)           # R2026: input -> LDO_EN, DNP

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    s.wires(vdd, (vdd[0], top)); s.wires(va, (va[0], top))
    s.wire(vdd[0], top, va[0], top)
    s.wire(vdd[0], top, vdd[0] - 5.08, top)
    s.label(vdd[0] - 5.08, top, "SI_VDD", justify="right bottom")
    s.wires(vc, (vc[0], top)); s.wires(vd, (vd[0], top))
    s.wire(vc[0], top, vd[0], top)
    s.wire(vd[0], top, vd[0] + 5.08, top)
    s.label(vd[0] + 5.08, top, "SI_VDD", justify="left bottom")
    s.wires(vb, (vb[0], top - 7.62), (vdd[0] - 5.08, top - 7.62))
    s.label(vdd[0] - 5.08, top - 7.62, "SI_VDDOB", justify="right bottom")
    # the two filtered supplies, drawn apart from the chip
    for xx, lab, vals in ((86.36, "SI_VDD", ("100n", "100n")), (121.92, "SI_VDDOB", ("100n", "10n"))):
        yy = 73.66
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    # --- CLK0 out to the squarer (band 2) -------------------------------------
    c0x, c0y = si.pin(13)
    s.wire(c0x, c0y, c0x + 12.7, c0y)
    s.glabel(c0x + 12.7, c0y, "HELPER_SRC", shape="output", justify="left")

    # --- CLK2: HO, buffered, on its own bank (item 10) -------------------------
    c2x, c2y = si.pin(9)
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    s.wire(55.88, ys, 62.23, ys)
    s.wire(69.85, ys, 88.9, ys)
    yh = ys - 15.24
    s.glabel(40.64, yh, "HELPER_SRC", shape="input", justify="right", rot=180)
    s.text(40.64, yh + 3.81, "10.0012344 MHz, 0/3.3 V CMOS, Si5351 CLK0", size=1.3, italic=True)
    s.wire(40.64, yh, 62.23, yh)
    r_h(s, 66.04, yh, R("R"), "0R")
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    s.wire(133.35, ys, *inv.pin(1))
    gnd(s, *inv.pin(2), drop=6.35, R=R)
    s.wire(inv.pin(5)[0], inv.pin(5)[1], inv.pin(5)[0], inv.pin(5)[1] - 2.54)
    s.label(inv.pin(5)[0], inv.pin(5)[1] - 2.54, "FO_VDD", justify="left bottom")
    s.junction(146.05, ys)
    s.wire(146.05, ys, 146.05, ys + 5.08)
    r_v(s, 146.05, ys + 8.89, R("R"), "1M 1%", left=True)
    a2 = inv.pin(3); y2 = inv.pin(4)
    s.wires((146.05, ys + 12.7), (146.05, ys + 16.51), (a2[0], ys + 16.51), a2)
    s.label(a2[0] - 2.54, ys + 16.51, "REPLICA", justify="right bottom")
    s.wire(y2[0], y2[1], y2[0] + 5.08, y2[1])
    s.label(y2[0] + 5.08, y2[1], "REPLICA", justify="left bottom")
    b = inv.pin(6)
    s.wire(b[0], b[1], b[0] + 12.7, b[1])
    s.glabel(b[0] + 12.7, b[1], "HELPER_SQ", shape="output", justify="left")
    s.text(132.08, ys + 24.13, "the same replica-biased squarer as every channel (item 18), "
           "on the fan-out's own supply", size=1.3, italic=True)

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        u = s.sym(LMK, lx, yl, 0, ref=R("U"), value="LMK1C1108PWR",
                  footprint="Package_SO:TSSOP-16_4.4x5mm_P0.65mm", lcsc="C2868241",
                  # 15 mm of capitals: clear of the body's corner and of the
                  # HELPER_SQ label below (2026-10-10)
                  ref_dxy=(-24.13, -12.7), val_dxy=(-24.13, -10.16))
        cx_, cy_ = u.pin(1)
        s.wire(cx_ - 7.62, cy_, cx_, cy_)
        s.glabel(cx_ - 7.62, cy_, "HELPER_SQ", shape="input", justify="right")
        gx, gy = u.pin(2)                       # 1G: pulled up (internal pull-down)
        # Flat, to the left of 1G (2026-10-10).  Standing up to an FO_VDD
        # label above, it ran through CLKIN's wire one pin higher, and the
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        s.wire(gx, gy, gx - 3.81, gy)
        r_h(s, gx - 7.62, gy, R("R"), "10k", below=True)
        s.wire(gx - 11.43, gy, gx - 13.97, gy)
        s.label(gx - 13.97, gy, "FO_VDD", justify="right bottom")
        vs_ = [u.pin(n) for n in (5, 10, 14)]
        tv = vs_[0][1] - 5.08
        for vp in vs_:
            s.wire(vp[0], vp[1], vp[0], tv)
        s.wire(vs_[0][0], tv, vs_[-1][0] + 5.08, tv)
        s.label(vs_[-1][0] + 5.08, tv, "FO_VDD", justify="left bottom")
        gs = [u.pin(n) for n in (4, 7, 12)]
        bv = gs[0][1] + 2.54
        for gp in gs:
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    for xx, vals in ((480.06, ("100n", "10n")), (515.62, ("100n", "100n"))):
        decouple(s, xx, 279.4, "+3V3_D", R, tall=False, values=vals)
        s.wire(xx, 279.4, xx, 281.94)
        s.label(xx, 281.94, "FO_VDD", justify="left bottom")
    # rev B item 19: taps on the reference at CLKIN, and on CLK0 at the Si5351
    s.junction(96.52, oy)
    ufl_tap(s, 96.52, oy, R("R"), R("J"), "TAP REF", R, up=True)
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    s.wire(ox + 22.86, oy, ox + 22.86, oy + 3.81)
    r_v(s, ox + 22.86, oy + 7.62, R("R"), "100k")
    gnd(s, ox + 22.86, oy + 11.43, drop=5.08, R=R)
    s.glabel(ox + 33.02, oy, "HTR_DRIVE", shape="output", justify="left")
    s.note(300.0, 246.0, 275.0, 0,
           "WHAT THE GATE DOES BEFORE SOFTWARE WRITES THE DAC.\n"
           "The 100k holds all three gates down whenever the DAC is not driving them, which "
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    # these seven nets arrive down the left-hand margin in a fixed order -- so
    # putting them on pins in that same order means none of them crosses
    # another.  Left to right on the board the margin lanes run I2C_SCL,
    # I2C_SDA, HTR_DRIVE, +3V3_D, +3V3_A, so those take pins 13, 11, 9, 7, 5.
    # ONEWIRE comes down from the probe block to the north and takes pin 3, and
    # +5V_HDR, which comes from the socket away to the east, takes pin 1, the
    # end nearest it.
    sigs = ["+5V_HDR", "ONEWIRE", "+3V3_A", "+3V3_D", "HTR_DRIVE",
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    s.wire(124.46, ioy, tv.pin(2)[0], tv.pin(2)[1])
    gnd(s, *tv.pin(1), drop=5.08, R=R)
    testpoint(s, 130.81, ioy, R("TP"), "TP_1W")
    s.glabel(137.16, ioy, "ONEWIRE", shape="bidirectional", justify="left")

    s.note(15.24, 142.0, 215.0, 0,
           "ADDRESSING IS NOT POSITIONAL, AND THAT MATTERS ON THE BENCH.\n"
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    rail(s, 255.27, YV, "+3V3_D", rise=6.35, R=R)
    s.wire(255.27, YV, XV, YV)
    s.wire(XV, YV, XV, js[-1].pin(2)[1])
    s.glabel(247.65, YW, "ONEWIRE", shape="bidirectional", justify="right", rot=180)
    s.wire(247.65, YW, XW, YW)
    s.wire(XW, YW, XW, js[-1].pin(1)[1])

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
